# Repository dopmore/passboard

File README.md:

# passboard
A simple nfc business card for Fallout 2026 in Shenzhen. An LED lights up the I in my name when a nfc tag gets scanned :)
(Slack @mmgg)

# PCB

# Schematics

# BOM

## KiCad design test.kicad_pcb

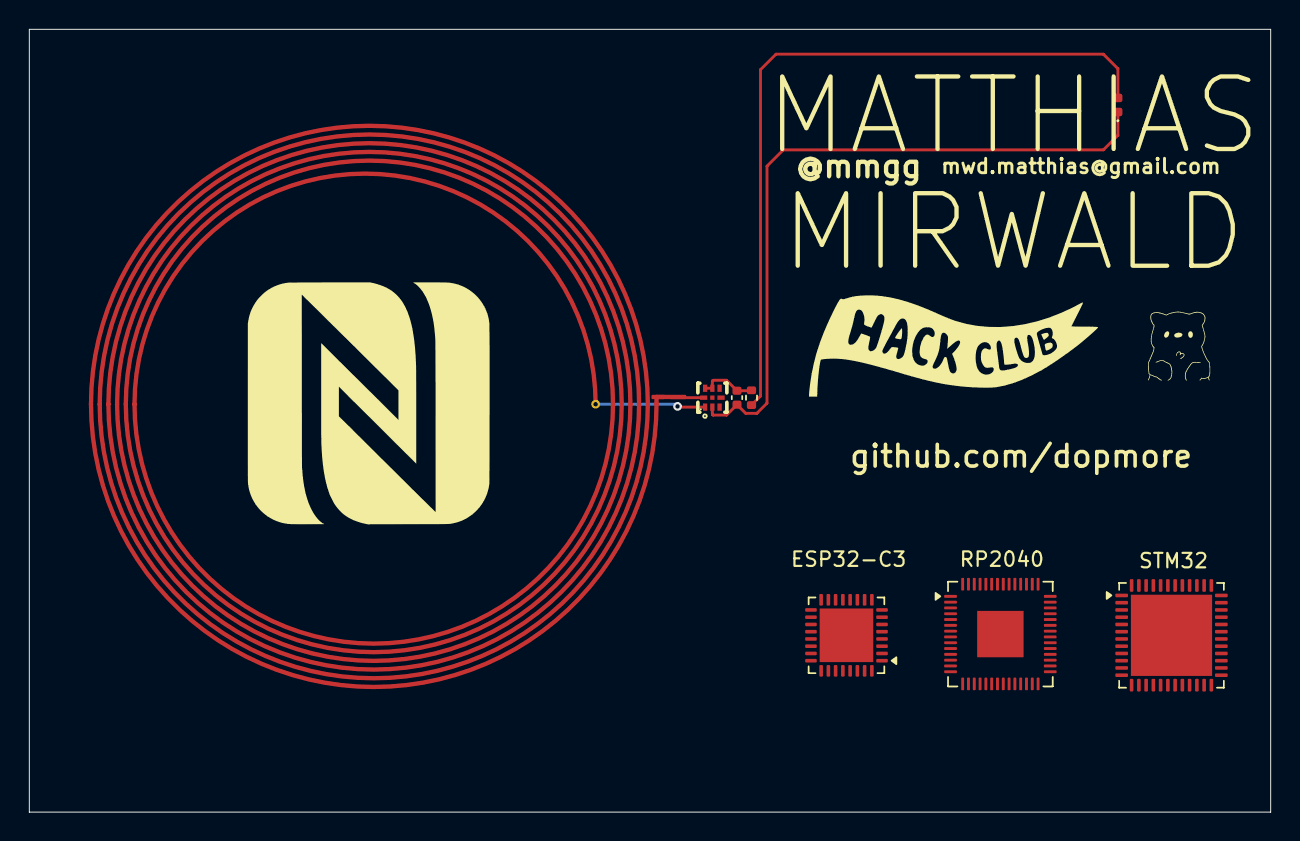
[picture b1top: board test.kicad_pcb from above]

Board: 2 copper layers, 85.6 x 54.0 mm, 8 parts (0 on the bottom side), 5 nets.

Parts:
C1: 220nF; C_0402_1005Metric
D1: LED; LED_0402_1005Metric
L1: L; COIL_GENERATOR
R1: 47; R_0402_1005Metric
U1: NT3H1101W0FHKH; XQFN-8_L1.6-W1.6-P0.50-BR
U2: ESP32-C3; QFN-32-1EP_5x5mm_P0.5mm_EP3.7x3.7mm
U3: RP2040; QFN-56-1EP_7x7mm_P0.4mm_EP3.2x3.2mm
U4: STM32; QFN-48-1EP_7x7mm_P0.5mm_EP5.6x5.6mm

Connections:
unnamed: D1.2 (A), R1.2
unnamed: C1.1, D1.1 (K), U1.2 (VSS)
unnamed: L1.2, U1.1 (LA)
unnamed: L1.1, U1.8 (LB)
unnamed: C1.2, R1.1, U1.6 (VCC), U1.7 (VOUT)

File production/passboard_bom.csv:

Designator,Footprint,Quantity,Value,LCSC Part #
C1,0402,1,220nF,
D1,0402,1,LED,
L1,COIL_GENERATOR,1,L,
R1,0402,1,47,
U1,XQFN-8_L1.6-W1.6-P0.50-BR,1,NT3H1101W0FHKH,C73156
